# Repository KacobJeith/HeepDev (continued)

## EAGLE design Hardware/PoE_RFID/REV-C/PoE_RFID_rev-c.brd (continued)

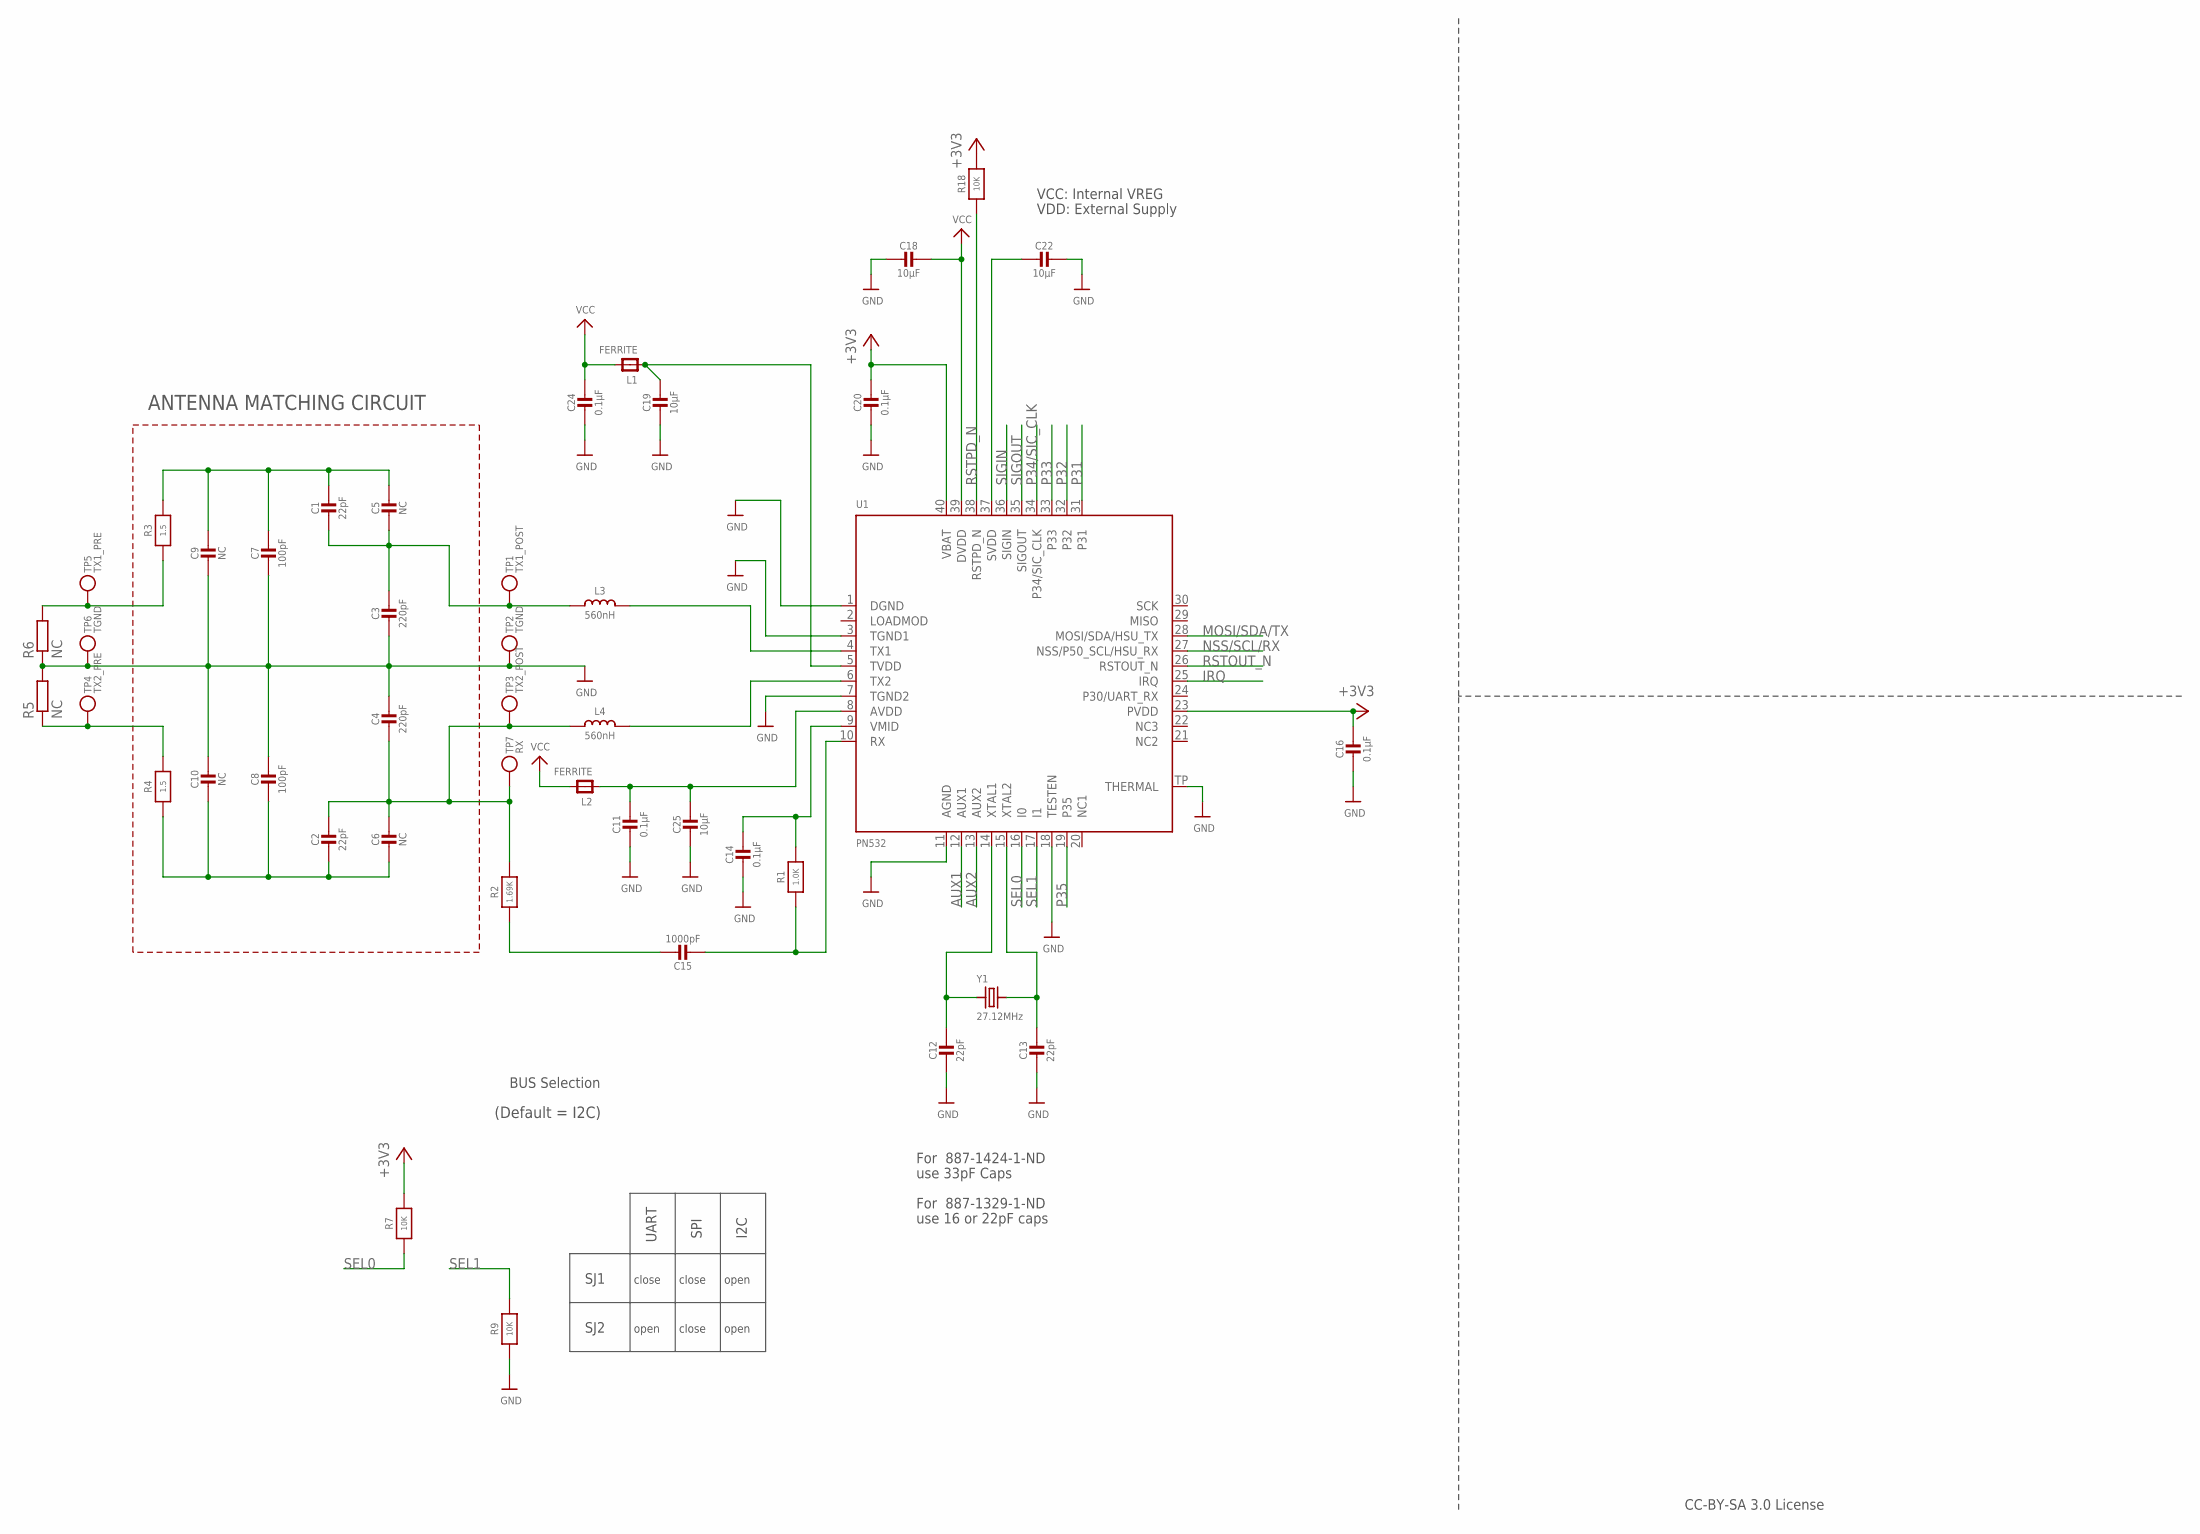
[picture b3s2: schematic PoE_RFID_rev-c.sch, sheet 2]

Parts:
C1, C2, C12, C13: 22pF; 0603-NO
C3, C4: 220pF; 0603-NO
C5, C6, C9, C10: NC; 0603-NO
C7, C8: 100pF; 0603-NO
C11, C14, C16, C20, C24: 0.1µF; 0603-NO
C15: 1000pF; 0603-NO
C18, C19, C22, C25: 10µF; 0603-NO
L1, L2: FERRITE; _0603
L3, L4: 560nH; 0603-NO
R1: 1.0K; 0603-NO@1
R2: 1.69K; 0603-NO@1
R3, R4: 1.5; 0603-NO@1
R5, R6: NC; R0201
R7, R9, R18: 10K; 0603-NO@1
TP1: TX1_POST; PAD-1.5X2.0
TP2, TP6: TGND; PAD-1.5X2.0
TP3: TX2_POST; PAD-1.5X2.0
TP4: TX2_PRE; PAD-1.5X2.0
TP5: TX1_PRE; PAD-1.5X2.0
TP7: RX; PAD-1.5X2.0
U1: PN532; HVQFN40-6X6
Y1: 27.12MHz; CRYSTAL_3.2X2.5

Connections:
+3V3: C16.1, C20.1, R7.2, R18.2, U1.23 (PVDD), U1.40 (VBAT); also elsewhere on the board
AUX1: U1.12 (AUX1)
AUX2: U1.13 (AUX2)
GND: C3.2, C4.1, C7.2, C8.1, C9.2, C10.1, C11.2, C12.2, C13.2, C14.2, C16.2, C18.2, C19.2, C20.2, C22.1, C24.2, C25.2, R5.2, R6.1, R9.1, TP2.P$1, TP6.P$1, U1.1 (DGND), U1.3 (TGND1), U1.7 (TGND2), U1.11 (AGND), U1.18 (TESTEN), U1.TP (THERMAL); also elsewhere on the board
IRQ: U1.25 (IRQ); also elsewhere on the board
MOSI/SDA/TX: U1.28 (MOSI/SDA/HSU_TX); also elsewhere on the board
unnamed: L3.2, U1.4 (TX1)
unnamed: L4.2, U1.6 (TX2)
unnamed: C1.2, C3.1, C5.2, L3.1, TP1.P$1
unnamed: R3.1, R6.2, TP5.P$1
unnamed: R4.2, R5.1, TP4.P$1
unnamed: C12.1, U1.14 (XTAL1), Y1.1
unnamed: C13.1, U1.15 (XTAL2), Y1.2
unnamed: C15.1, R2.1
unnamed: C14.1, R1.2, U1.9 (VMID)
unnamed: C15.2, R1.1, U1.10 (RX)
unnamed: C2.1, C4.2, C6.1, L4.1, R2.2, TP3.P$1, TP7.P$1
unnamed: C11.1, C25.1, L2.1, U1.8 (AVDD)
unnamed: C19.1, L1.1, U1.5 (TVDD)
unnamed: C22.2, U1.37 (SVDD)
NSS/SCL/RX: U1.27 (NSS/P50_SCL/HSU_RX); also elsewhere on the board
P31: U1.31
P32: U1.32
P33: U1.33
P34/SIC_CLK: U1.34 (P34/SIC_CLK)
P35: U1.19 (P35)
RSTOUT_N: U1.26 (RSTOUT_N)
RSTPD_N: R18.1, U1.38 (RSTPD_N); also elsewhere on the board
SEL0: R7.1, U1.16 (I0)
SEL1: R9.2, U1.17 (I1)
SIGIN: U1.36 (SIGIN)
SIGOUT: U1.35 (SIGOUT)
TX1_ANTENNA: C1.1, C5.1, C7.1, C9.1, R3.2
TX2_ANTENNA: C2.2, C6.2, C8.2, C10.2, R4.1
VCC: C18.1, C24.1, L1.2, L2.2, U1.39 (DVDD)

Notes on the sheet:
ANTENNA MATCHING CIRCUIT
SJ1
SJ2
UART
SPI
I2C
close
open
CC-BY-SA 3.0 License
For 887-1329-1-ND
use 16 or 22pF caps
For 887-1424-1-ND
use 33pF Caps
BUS Selection
(Default = I2C)
VCC: Internal VREG
VDD: External Supply

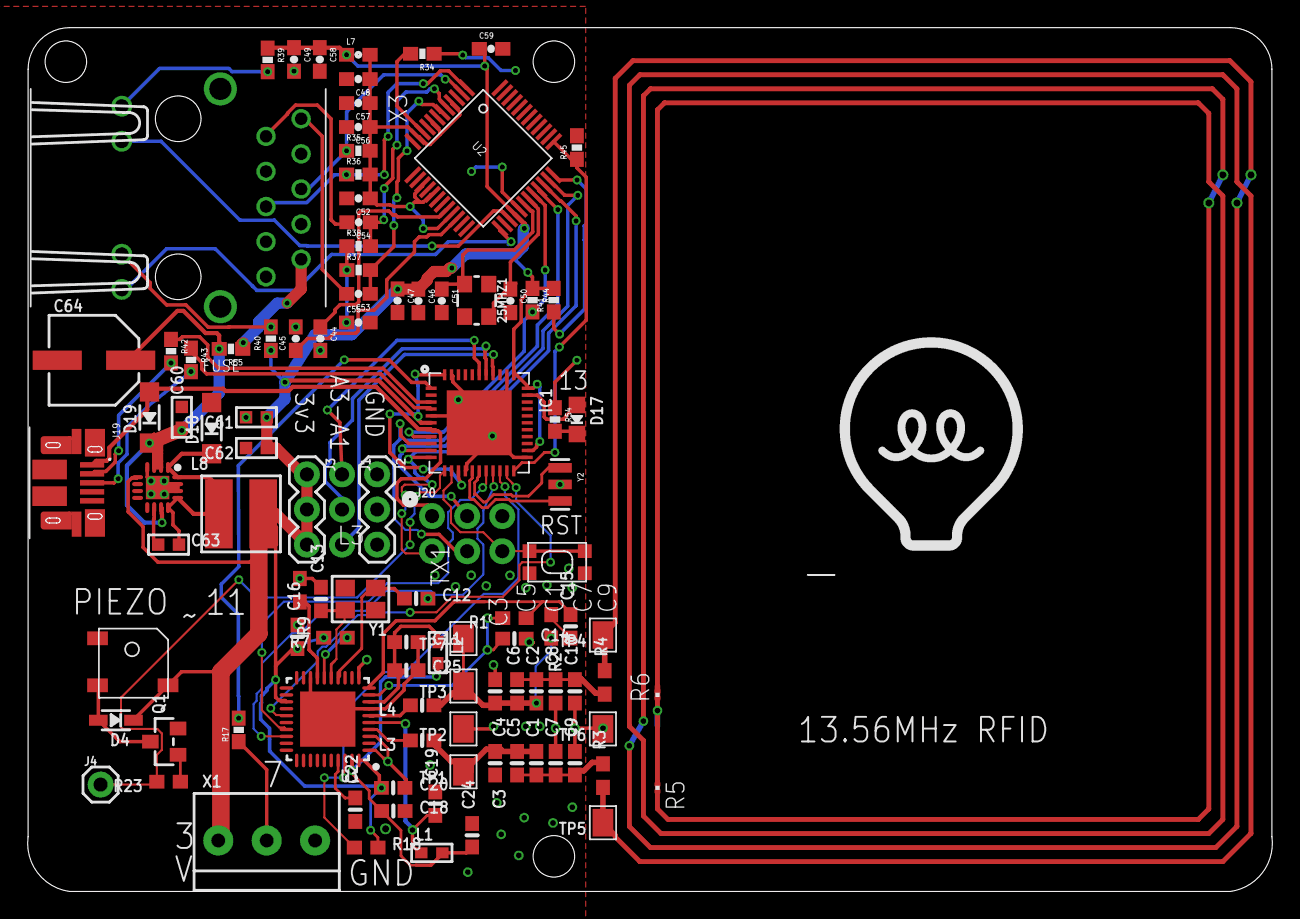
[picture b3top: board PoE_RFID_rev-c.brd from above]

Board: 2 copper layers, 90.0 x 62.5 mm, 104 parts (0 on the bottom side), 70 nets.

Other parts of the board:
U$19: HEEPLOGO
